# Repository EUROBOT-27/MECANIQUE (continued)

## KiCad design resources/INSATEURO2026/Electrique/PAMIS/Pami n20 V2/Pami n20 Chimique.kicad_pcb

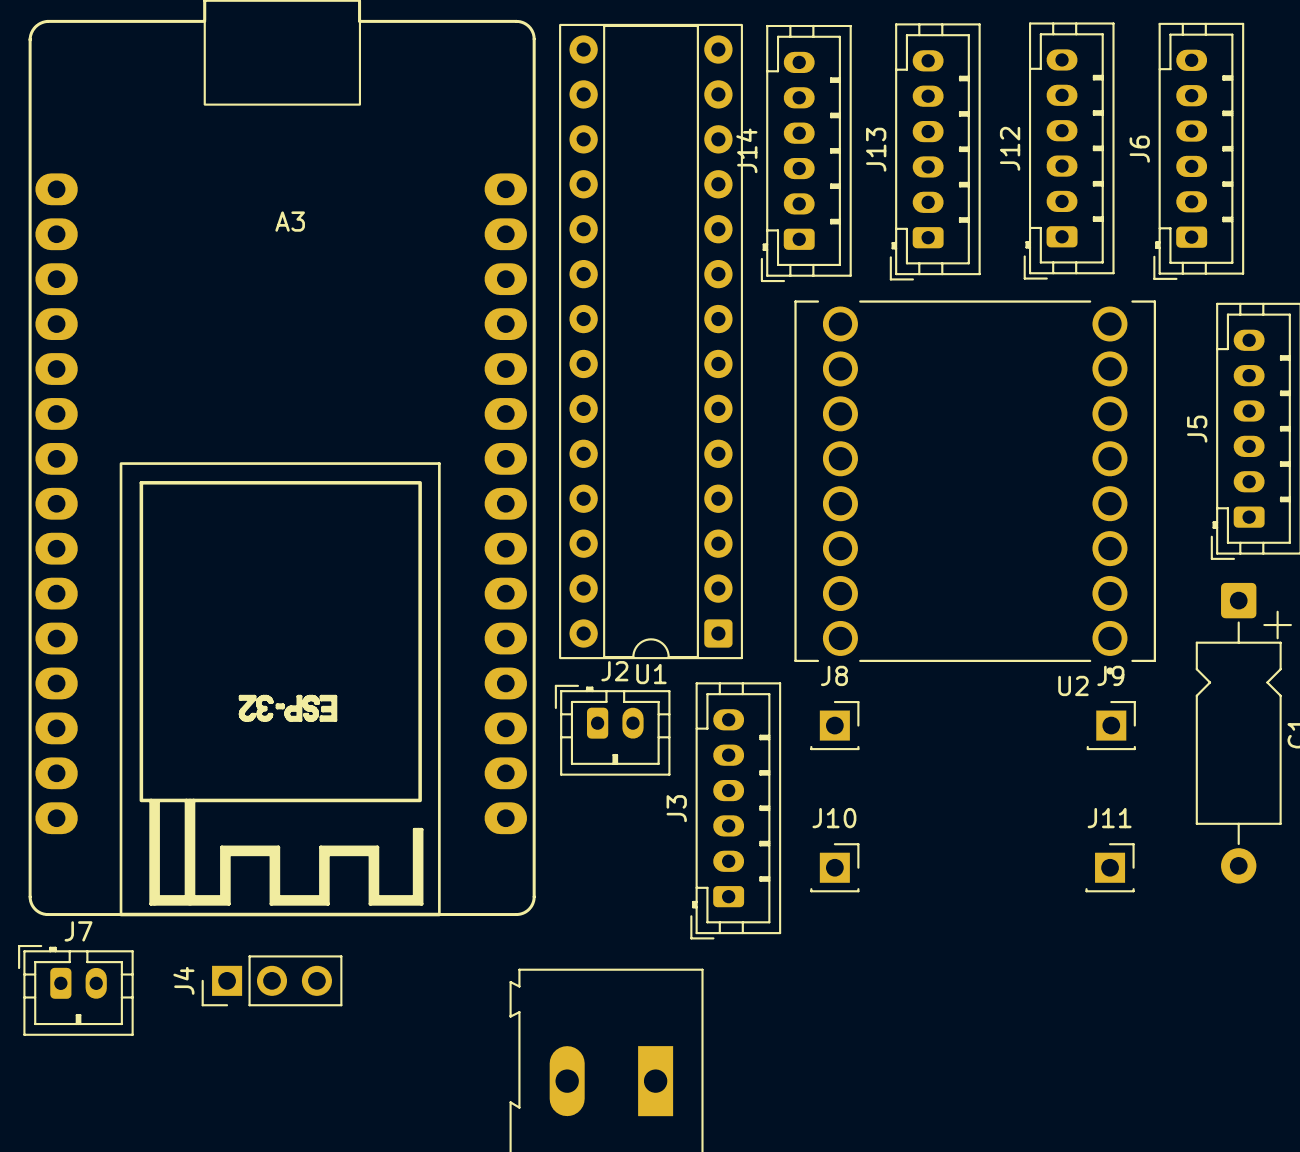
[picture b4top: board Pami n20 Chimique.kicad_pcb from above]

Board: 2 copper layers, 18 parts (0 on the bottom side), 31 nets, no tracks yet.

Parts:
A3: ESP32_DevKit_V1_DOIT_30GPIOs; DOIT_ESP32_DEVKIT_30Pins
C1: C_Polarized; CP_Axial_L10.0mm_D4.5mm_P15.00mm_Horizontal
J1: Screw_Terminal_01x02; TerminalBlock_Altech_AK300-2_P5.00mm
J2: URG; JST_PH_B2B-PH-K_1x02_P2.00mm_Vertical
J3: ENC2; JST_PH_B6B-PH-K_1x06_P2.00mm_Vertical
J4: Servo Connector; PinHeader_1x03_P2.54mm_Vertical
J5: ENC1; JST_PH_B6B-PH-K_1x06_P2.00mm_Vertical
J6: TOF1; JST_PH_B6B-PH-K_1x06_P2.00mm_Vertical
J7: Jack; JST_PH_B2B-PH-K_1x02_P2.00mm_Vertical
J8, J9, J10, J11: PINHD_1x1_Female; PinSocket_1x01_P2.54mm_Vertical
J12: TOF2; JST_PH_B6B-PH-K_1x06_P2.00mm_Vertical
J13: TOF3; JST_PH_B6B-PH-K_1x06_P2.00mm_Vertical
J14: TOF4; JST_PH_B6B-PH-K_1x06_P2.00mm_Vertical
U1: MCP23017_SP; DIP-28_W7.62mm_Socket
U2: ROB-14450; MODULE_ROB-14450

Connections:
+3.3V: A3.1 (3.3V), C1.1, J6.3, J12.3, J13.3, J14.3, U1.9 (VDD), U2.2 (VCC)
+5V: A3.30 (VIN), J3.2, J4.2, J5.2, J9.1, U2.1 (VM), U2.13 (STBY)
A1: J5.1, U2.4 (A01)
A2: J5.6, U2.5 (A02)
B1: J3.1, U2.7 (B01)
B2: J3.6, U2.6 (B02)
ENC1_A: A3.22 (ADC1_CH4/D33), J5.4
ENC1_B: A3.21 (ADC1_CH4/D32), J5.3
ENC2_A: A3.20 (ADC1_CH7/D35), J3.4
ENC2_B: A3.19 (ADC1_CH6/D34), J3.3
GND: A3.2 (GND), C1.2, J1.1, J3.5, J4.3, J5.5, J6.4, J7.2, J10.1, J11.1, J12.4, J13.4, J14.4, U1.10 (VSS), U1.15 (A0), U1.16 (A1), U1.17 (A2), U2.3 (GND), U2.8 (GND), U2.9 (GND)
GPIO1: J6.2, U1.1 (GPB0)
GPIO2: J12.2, U1.2 (GPB1)
GPIO3: J13.2, U1.3 (GPB2)
GPIO4: J14.2, U1.4 (GPB3)
JACK: A3.15 (D23), J7.1
M1_PWM: A3.8 (D5), U2.16 (PWMA)
M2_PWM: A3.27 (ADC2_CH5/D12), U2.10 (PWMB)
MOT_AIN1: U1.27 (GPA6), U2.14 (AI1)
MOT_AIN2: U1.28 (GPA7), U2.15 (AI2)
MOT_BIN1: U1.26 (GPA5), U2.12 (BI1)
MOT_BIN2: U1.25 (GPA4), U2.11 (BI2)
unnamed: J1.2, J2.1
SCL: A3.14 (D22/SCL), J6.5, J12.5, J13.5, J14.5, U1.12 (SCK)
SDA: A3.11 (D21/SDA), J6.6, J12.6, J13.6, J14.6, U1.13 (SDA)
SERVO_PWM: A3.9 (D18), J4.1
Supply: J2.2, J8.1
XShunt1: J6.1, U1.24 (GPA3)
XShunt2: J12.1, U1.23 (GPA2)
XShunt3: J13.1, U1.22 (GPA1)
XShunt4: J14.1, U1.21 (GPA0)

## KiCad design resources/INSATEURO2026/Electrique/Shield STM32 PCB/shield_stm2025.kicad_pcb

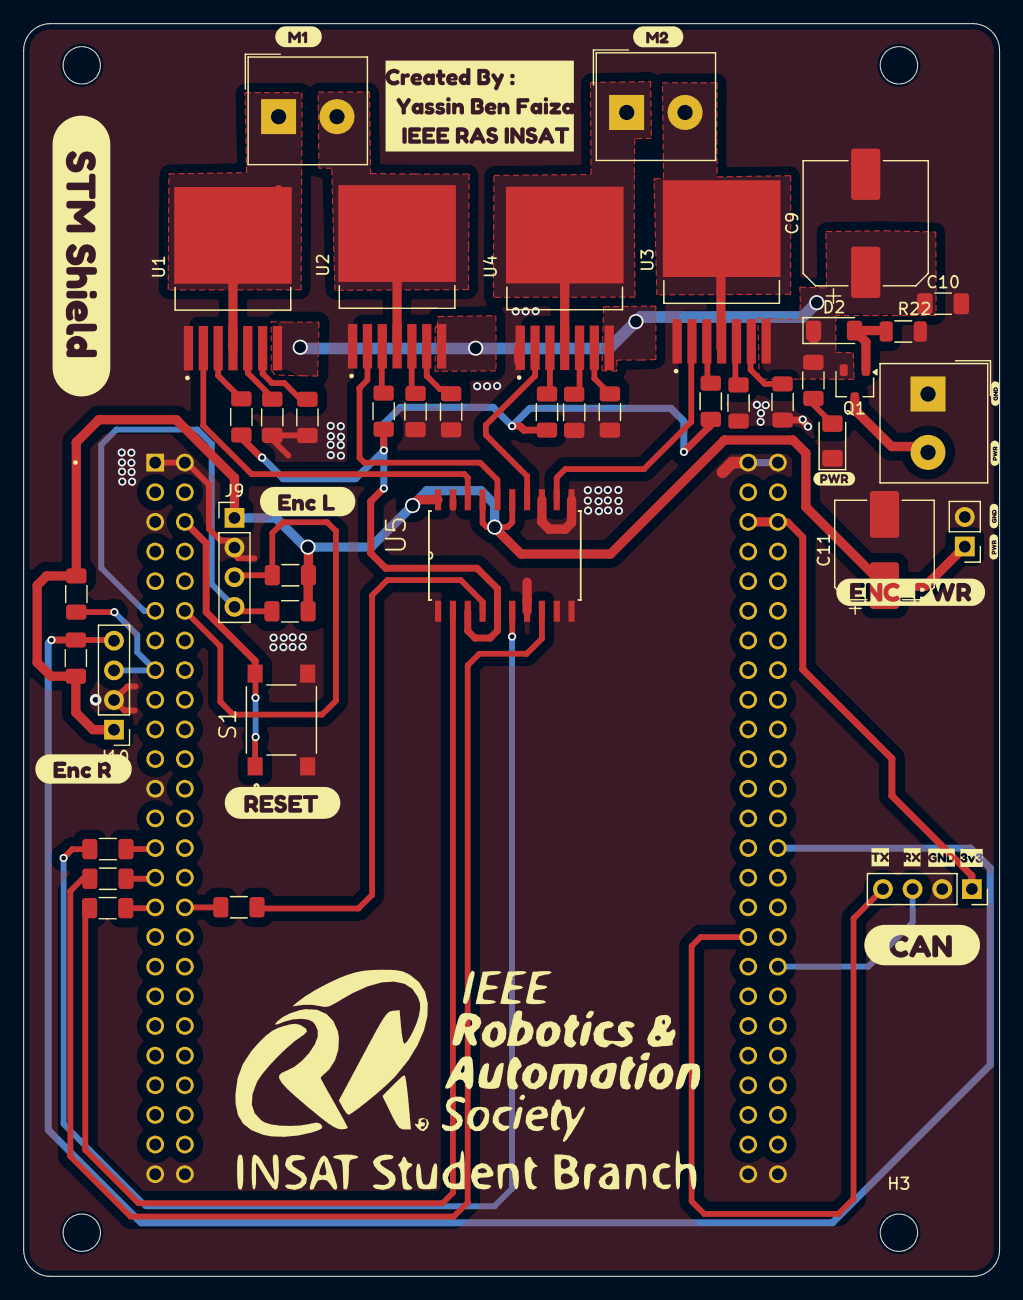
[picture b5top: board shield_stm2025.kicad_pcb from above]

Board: 2 copper layers, 83.6 x 107.3 mm, 64 parts (0 on the bottom side), 43 nets.

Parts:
C9: 470u; CP_Elec_10x10.5
C10: 100n; C_1206_3216Metric_Pad1.33x1.80mm_HandSolder
C11: 10u; CP_Elec_8x5.4
D1: LED; LED_1206_3216Metric_Pad1.42x1.75mm_HandSolder
D2: BZV55B10; D_MiniMELF
H1, H2, H3, H4: MountingHole; MountingHole_3.2mm_M3
J2: OUT M1; Altech_AK100_1x02_P5.00mm
J3: OUT M2; Altech_AK100_1x02_P5.00mm
J4: 24V input; Altech_AK100_1x02_P5.00mm
J6: CAN; PinSocket_1x04_P2.54mm_Vertical
J8: Alimentation; PinHeader_1x02_P2.54mm_Vertical
J9: Encoder_Left; PinHeader_1x04_P2.54mm_Vertical
J10: Encoder_Right; PinHeader_1x04_P2.54mm_Vertical
Q1: AO3401A; SOT-23W
R1, R2, R5, R6, R9, R10, R15, R16: 10K; R_1206_3216Metric_Pad1.30x1.75mm_HandSolder
R3, R4, R7, R8, R11, R12, R13, R14: 4.7K; R_1206_3216Metric_Pad1.30x1.75mm_HandSolder
R17, R18, R19, R20, R21: R; R_1206_3216Metric_Pad1.30x1.75mm_HandSolder
R22: 10K; R_1206_3216Metric
S1: PTS645SK50SMTR92LFS; SW_PTS645SK50SMTR92LFS
TB1: STM32F4DISCOVERY; MODULE_STM32F407G-DISC1
U1, U2, U3, U4: BTS7960B; DPAK127P1490X440-8N
U5: 74HC244; SOIC127P1032X265-20N
kibuzzard-6821E684: G***; kibuzzard-6821E684
kibuzzard-6821EA5D: G***; kibuzzard-6821EA5D
kibuzzard-6821EA78: G***; kibuzzard-6821EA78
kibuzzard-6821EB0D: G***; kibuzzard-6821EB0D
kibuzzard-6821EB1E: G***; kibuzzard-6821EB1E
kibuzzard-6821EB6B: G***; kibuzzard-6821EB6B
kibuzzard-6821FFFF: G***; kibuzzard-6821FFFF
kibuzzard-6824CA9A, kibuzzard-6824CA9A#2: G***; kibuzzard-6824CA9A
kibuzzard-6824CA75, kibuzzard-6824CA75#2: G***; kibuzzard-6824CA75
kibuzzard-6824CD1D: G***; kibuzzard-6824CD1D
kibuzzard-6824CD32: G***; kibuzzard-6824CD32
kibuzzard-6824CD49: G***; kibuzzard-6824CD49
kibuzzard-6824CD70: G***; kibuzzard-6824CD70
kibuzzard-6881FAE2: G***; kibuzzard-6881FAE2
kibuzzard-68220201: G***; kibuzzard-68220201
kibuzzard-68220375: G***; kibuzzard-68220375

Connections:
+3.3V: J6.1, TB1.P2_5 (3V), TB1.P2_6 (3V)
EN: R2.1, R6.1, R10.2, R15.2, U5.3 (2Y0), U5.5 (2Y1)
GND: C9.2, C10.2, C11.2, D1.1 (K), J4.1, J6.2, J8.2, J9.2, J10.2, R3.1, R4.2, R7.1, R8.2, R11.1, R12.2, R13.2, R14.1, R22.2, S1.3, S1.4, TB1.P1_1 (GND), TB1.P1_2 (GND), TB1.P1_5 (GND), TB1.P1_23 (GND), TB1.P1_49 (GND), TB1.P1_50 (GND), TB1.P2_1 (GND), TB1.P2_2 (GND), TB1.P2_49 (GND), TB1.P2_50 (GND), U1.1 (GND), U2.1 (GND), U3.1 (GND), U4.1 (GND), U5.1 (1OE), U5.7 (2Y2), U5.9 (2Y3), U5.10 (GND), U5.11 (2A3), U5.13 (2A2), U5.19 (2OE)
LPWM1: R1.1, TB1.P1_32 (PE14)
LPWM2: R16.1, TB1.P1_29 (PE11)
NRST: S1.1, S1.2, TB1.P1_6 (NRST)
unnamed: D1.2 (A), R17.2
unnamed: D2.2 (A), Q1.1 (G), R22.1
unnamed: J2.1, U1.4 (OUT), U1.8 (OUT)
unnamed: J2.2, U2.4 (OUT), U2.8 (OUT)
unnamed: J3.1, U4.4 (OUT), U4.8 (OUT)
unnamed: J3.2, U3.4 (OUT), U3.8 (OUT)
unnamed: J4.2, Q1.3 (D)
unnamed: R2.2, U1.3 (INH)
unnamed: R4.1, U1.6 (IS)
unnamed: R3.2, U1.5 (SR)
unnamed: R15.1, U2.3 (INH)
unnamed: R8.1, U2.6 (IS)
unnamed: R7.2, U2.5 (SR)
unnamed: R10.1, U3.3 (INH)
unnamed: R13.1, U3.6 (IS)
unnamed: R11.2, U3.5 (SR)
unnamed: R6.2, U4.3 (INH)
unnamed: R12.1, U4.6 (IS)
unnamed: R14.2, U4.5 (SR)
unnamed: R9.2, U5.2 (1A0)
unnamed: R1.2, U5.4 (1A1)
unnamed: R5.2, U5.6 (1A2)
unnamed: R16.2, U5.8 (1A3)
OUT1: U1.2 (IN), U5.18 (1Y0)
OUT2: U2.2 (IN), U5.16 (1Y1)
OUT3: U4.2 (IN), U5.14 (1Y2)
OUT4: U3.2 (IN), U5.12 (1Y3)
PA0: J9.3, R20.1, TB1.P1_12 (PA0-WKUP)
PA1: J9.4, R21.1, TB1.P1_11 (PA1)
PA5: J10.3, R18.1, TB1.P1_15 (PA5)
PB3: J10.4, R19.1, TB1.P2_28 (PB3)
RPWM1: R9.1, TB1.P1_31 (PE13)
RPWM2: R5.1, TB1.P1_27 (PE9)
RX: J6.3, TB1.P2_36 (PD0)
Supply: C9.1, C10.1, D2.1 (K), Q1.2 (S), R17.1, U1.7 (VS), U2.7 (VS), U3.7 (VS), U4.7 (VS)
TX: J6.4, TB1.P2_33 (PD1)
VCC: C11.1, J8.1, J9.1, J10.1, R18.2, R19.2, R20.2, R21.2, U5.15 (2A1), U5.17 (2A0), U5.20 (VCC)

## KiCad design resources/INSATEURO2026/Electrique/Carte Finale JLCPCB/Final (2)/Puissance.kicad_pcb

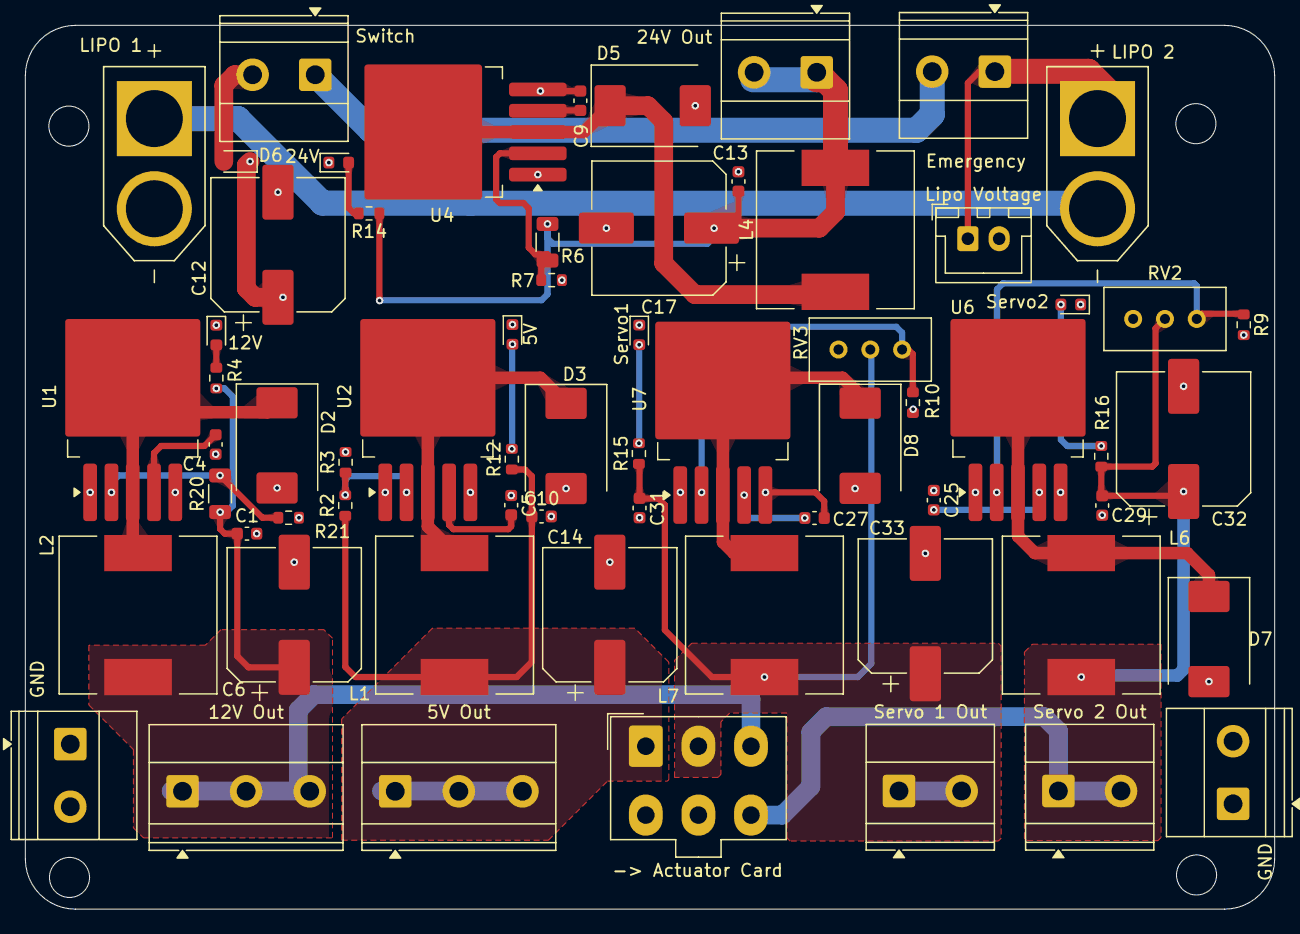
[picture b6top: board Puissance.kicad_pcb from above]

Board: 4 copper layers, 99.8 x 70.6 mm, 65 parts (0 on the bottom side), 31 nets.

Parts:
5V, 12V, 24V: LED; LED_0603_1608Metric
5V Out: 5V; TerminalBlock_Phoenix_MKDS-1,5-3-5.08_1x03_P5.08mm_Horizont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
12V Out: 12V; TerminalBlock_Phoenix_MKDS-1,5-3-5.08_1x03_P5.08mm_Horizont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
24V Out: 24V Out; TerminalBlock_Phoenix_MKDS-1,5-2_1x02_P5.00mm_Horizontal
-> Actuator Card: Conn_02x03; Molex_Mini-Fit_Jr_5566-06A_2x03_P4.20mm_Vertical
C1, C4, C5, C9, C10, C13, C25, C27, C29, C31: 105; C_0603_1608Metric
C6, C14, C17, C32, C33: 330u; CP_Elec_10x10.5
C12: 1000u; CP_Elec_10x10.5
D2, D3, D5, D7, D8: B540C; D_SMC
D6: SS34; D_SOD-323
Emergency: Emergency Stop; TerminalBlock_Phoenix_MKDS-1,5-2_1x02_P5.00mm_Horizontal
GND: ADJ out; TerminalBlock_Phoenix_MKDS-1,5-2_1x02_P5.00mm_Horizontal
GND : ADJ out; TerminalBlock_Phoenix_MKDS-1,5-2_1x02_P5.00mm_Horizontal
L1, L2, L4, L6, L7: 47uH; L_12x12mm_H6mm
LIPO 1, LIPO 2: XT60-M; AMASS_XT60-M
Lipo Voltage: LIPO 1 VOLT; JST_XH_B2B-XH-A_1x02_P2.50mm_Vertical
R2: 10K; R_0603_1608Metric
R3, R7, R9, R10: 3.3K; R_0603_1608Metric
R4: 1k; R_0603_1608Metric
R6: 60.4K; R_1206_3216Metric
R12: 220; R_0603_1608Metric
R14: 3.3k; R_0603_1608Metric
R15, R16: 1K; R_0603_1608Metric
R20: 13K; R_1206_3216Metric
R21: 1.5K; R_0603_1608Metric
RV2, RV3: R_Potentiometer; Potentiometer_Bourns_3296W_Vertical
Servo1, Servo2: LED; LED_0603_1608Metric
Servo 1 Out, Servo 2 Out: ADJ out; TerminalBlock_Phoenix_MKDS-1,5-2_1x02_P5.00mm_Horizontal
Switch: Master Switch; TerminalBlock_Phoenix_MKDS-1,5-2_1x02_P5.00mm_Horizontal
U1, U2, U4, U6, U7: XL4015; TO-263-5_TabPin3

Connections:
5V: 5V Out.1, 5V Out.2, 5V Out.3, -> Actuator Card.1, C10.1, C14.1, L1.2, R2.1, R12.1
12V: 12V Out.1, 12V Out.2, 12V Out.3, -> Actuator Card.3, C1.1, C6.1, L2.2, R4.1, R20.1
24V: 24V Out.1, 24V Out.2, C13.1, C17.1, L4.2, R6.1, R14.1
ADJ1: -> Actuator Card.6, C29.1, C32.1, L6.2, R16.1, RV2.2, Servo 2 Out.1, Servo 2 Out.2
GND: 5V.1 (K), 12V.1 (K), 24V.1 (K), -> Actuator Card.4, -> Actuator Card.5, C1.2, C6.2, C10.2, C12.2, C13.2, C14.2, C17.2, C29.2, C31.2, C32.2, C33.2, D2.2 (A), D3.2 (A), D5.2 (A), D7.2 (A), D8.2 (A), GND.1, GND.2, GND.1, GND.2, LIPO 1.N (NEG), Lipo Voltage.2, R3.2, R7.2, R9.2, R10.2, R21.2, RV2.3, RV3.3, Servo1.1 (K), Servo2.1 (K), U1.1 (GND), U2.1 (GND), U4.1 (GND), U6.1 (GND), U7.1 (GND)
unnamed: D2.1 (K), L2.1, U1.3 (SW)
unnamed: D3.1 (K), L1.1, U2.3 (SW)
unnamed: 12V.2 (A), R4.2
unnamed: D5.1 (K), L4.1, U4.3 (SW)
unnamed: D7.1 (K), L6.1, U6.3 (SW)
unnamed: D8.1 (K), L7.1, U7.3 (SW)
unnamed: 5V.2 (A), R12.2
unnamed: 24V.2 (A), R14.2
unnamed: R15.2, Servo1.2 (A)
unnamed: R16.2, Servo2.2 (A)
unnamed: LIPO 1.P (POS), LIPO 2.N (NEG)
unnamed: Emergency.1, LIPO 2.P (POS), Lipo Voltage.1
unnamed: Emergency.2, Switch.1
unnamed: R20.2, R21.1, U1.2 (FB)
unnamed: C4.2, U1.4 (VC)
unnamed: R2.2, R3.1, U2.2 (FB)
unnamed: C5.2, U2.4 (VC)
unnamed: R6.2, R7.1, U4.2 (FB)
unnamed: C9.2, U4.4 (VC)
unnamed: R9.1, RV2.1, U6.2 (FB)
unnamed: C25.2, U6.4 (VC)
unnamed: R10.1, RV3.1, U7.2 (FB)
unnamed: C27.2, U7.4 (VC)
SERVO: -> Actuator Card.2, C31.1, C33.1, L7.2, R15.1, RV3.2, Servo 1 Out.1, Servo 1 Out.2
SUPPLY: D6.2 (A), Switch.2
VDC: C4.1, C5.1, C9.1, C12.1, C25.1, C27.1, D6.1 (K), U1.5 (VIN), U2.5 (VIN), U4.5 (VIN), U6.5 (VIN), U7.5 (VIN)

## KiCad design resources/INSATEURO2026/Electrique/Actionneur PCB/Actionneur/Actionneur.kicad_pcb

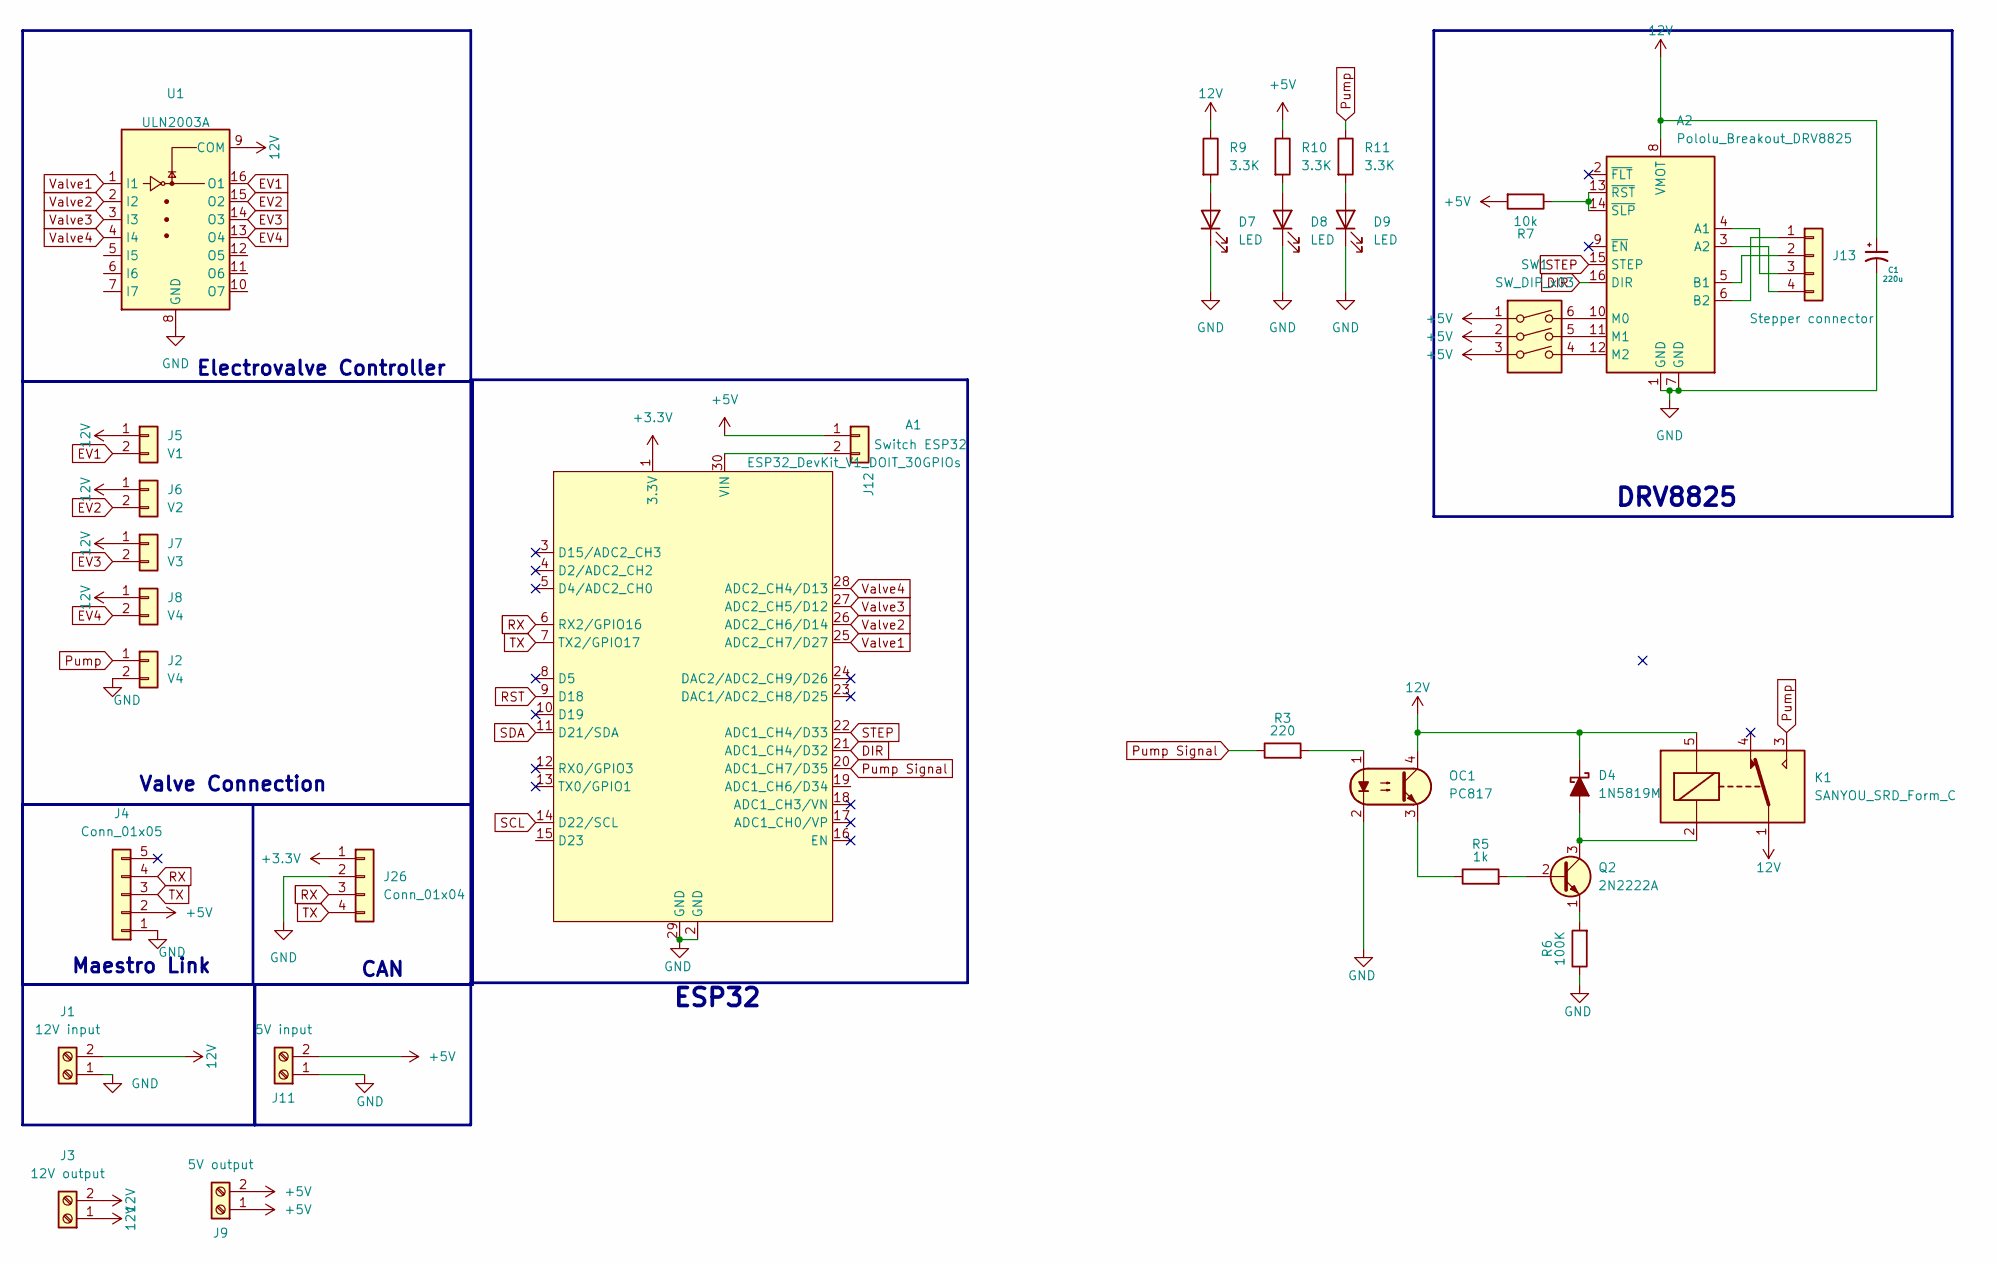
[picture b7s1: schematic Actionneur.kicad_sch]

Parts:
A1: ESP32_DevKit_V1_DOIT_30GPIOs; DOIT_ESP32_DEVKIT_30Pins
A2: Pololu_Breakout_DRV8825; Pololu_Breakout-16_15.2x20.3mm
C1: 220u; CP_Elec_10x10.5
D4: 1N5819M; D_SMC
D7, D8, D9: LED; LED_0603_1608Metric
J1: 12V input; Altech_AK100_1x02_P5.00mm
J2, J8: V4; JST_PH_B2B-PH-K_1x02_P2.00mm_Vertical
J3: 12V output; Altech_AK100_1x02_P5.00mm
J4: Conn_01x05; JST_EH_B5B-EH-A_1x05_P2.50mm_Vertical
J5: V1; JST_PH_B2B-PH-K_1x02_P2.00mm_Vertical
J6: V2; JST_PH_B2B-PH-K_1x02_P2.00mm_Vertical
J7: V3; JST_PH_B2B-PH-K_1x02_P2.00mm_Vertical
J9: 5V output; Altech_AK100_1x02_P5.00mm
J11: 5V input; Altech_AK100_1x02_P5.00mm
J12: Switch ESP32; PinHeader_1x02_P1.00mm_Vertical
J13: Stepper connector; JST_EH_B4B-EH-A_1x04_P2.50mm_Vertical
J26: Conn_01x04; JST_EH_B4B-EH-A_1x04_P2.50mm_Vertical
K1: SANYOU_SRD_Form_C; Relay_SPDT_SANYOU_SRD_Series_Form_C
OC1: PC817; Vishay_CNY64
Q2: 2N2222A; TO-18-3_EBC
R3: 220; R_0603_1608Metric
R5: 1k; R_0603_1608Metric
R6: 100K; R_0603_1608Metric
R7: 10k; R_Axial_DIN0204_L3.6mm_D1.6mm_P7.62mm_Horizontal
R9, R10, R11: 3.3K; R_0603_1608Metric
SW1: SW_DIP_x03; SW_DIP_SPSTx03_Slide_9.78x9.8mm_W7.62mm_P2.54mm
U1: ULN2003A; DIP-16_W7.62mm

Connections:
12V: A2.8 (VMOT), C1.1, D4.1 (K), J1.2, J3.1, J3.2, J5.1, J6.1, J7.1, J8.1, K1.1, K1.5, OC1.4, R9.1, U1.9 (COM)
+3.3V: A1.1 (3.3V), J26.1
+5V: J4.2, J9.1, J9.2, J11.2, J12.1, R7.2, R10.1, SW1.1, SW1.2, SW1.3
DIR: A1.21 (ADC1_CH4/D32), A2.16 (DIR)
EV1: J5.2, U1.16 (O1)
EV2: J6.2, U1.15 (O2)
EV3: J7.2, U1.14 (O3)
EV4: J8.2, U1.13 (O4)
GND: A1.2 (GND), A1.29 (GND), A2.1 (GND), A2.7 (GND), C1.2, D7.1 (K), D8.1 (K), D9.1 (K), J1.1, J2.2, J4.1, J11.1, J26.2, OC1.2, R6.1, U1.8 (GND)
unnamed: A1.30 (VIN), J12.2
unnamed: A2.4 (A1), J13.3
unnamed: A2.3 (A2), J13.4
unnamed: A2.5 (B1), J13.2
unnamed: A2.6 (B2), J13.1
unnamed: A2.10 (M0), SW1.6
unnamed: A2.11 (M1), SW1.5
unnamed: A2.12 (M2), SW1.4
unnamed: A2.13 (~RST), A2.14 (~SLP), R7.1
unnamed: D4.2 (A), K1.2, Q2.3 (C)
unnamed: D7.2 (A), R9.2
unnamed: D8.2 (A), R10.2
unnamed: D9.2 (A), R11.2
unnamed: OC1.1, R3.2
unnamed: OC1.3, R5.1
unnamed: Q2.2 (B), R5.2
unnamed: Q2.1 (E), R6.2
Pump: J2.1, K1.3, R11.1
Pump Signal: A1.20 (ADC1_CH7/D35), R3.1
RST: A1.9 (D18)
RX: A1.6 (RX2/GPIO16), J4.4, J26.3
SCL: A1.14 (D22/SCL)
SDA: A1.11 (D21/SDA)
STEP: A1.22 (ADC1_CH4/D33), A2.15 (STEP)
TX: A1.7 (TX2/GPIO17), J4.3, J26.4
Valve1: A1.25 (ADC2_CH7/D27), U1.1 (I1)
Valve2: A1.26 (ADC2_CH6/D14), U1.2 (I2)
Valve3: A1.27 (ADC2_CH5/D12), U1.3 (I3)
Valve4: A1.28 (ADC2_CH4/D13), U1.4 (I4)

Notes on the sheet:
DRV8825
ESP32
Electrovalve Controller
CAN
Valve Connection
Maestro Link

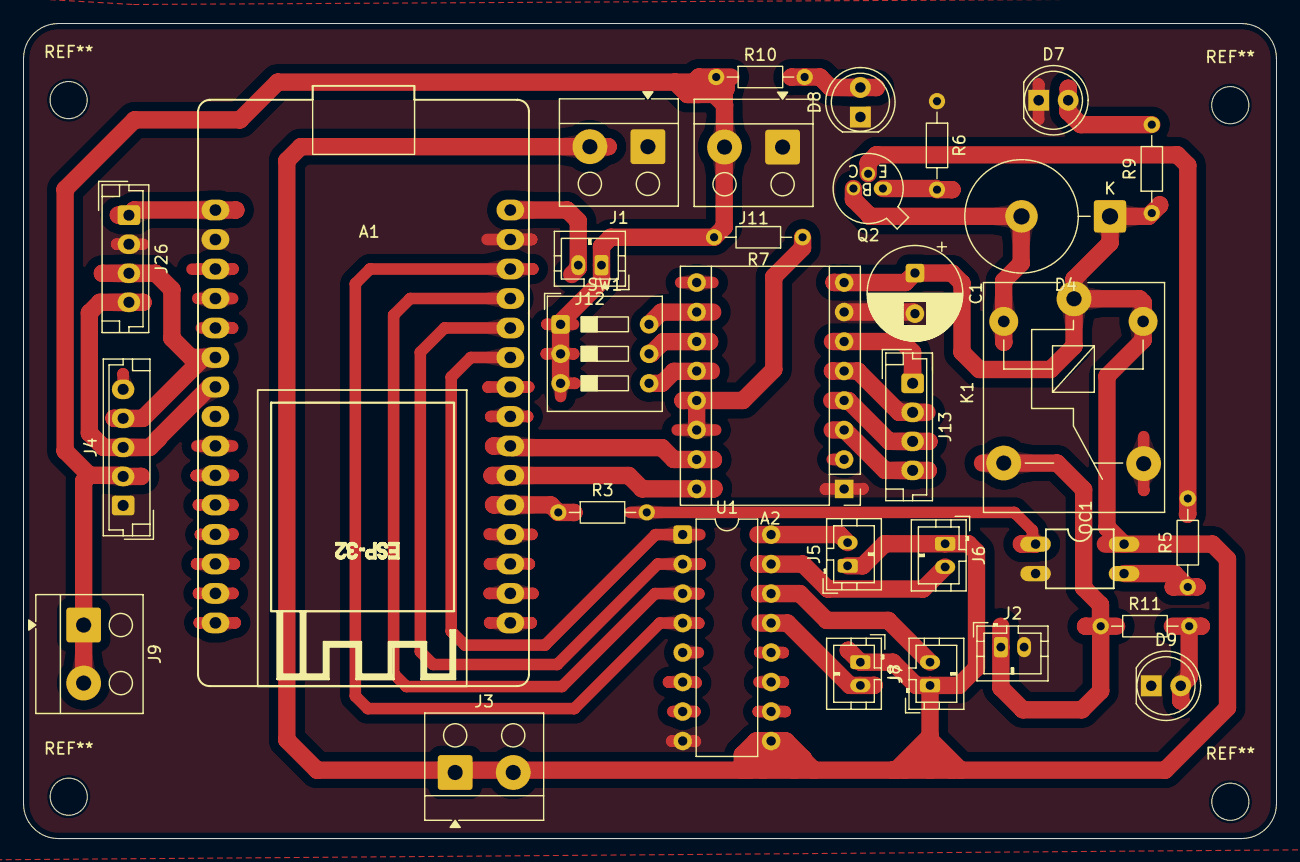
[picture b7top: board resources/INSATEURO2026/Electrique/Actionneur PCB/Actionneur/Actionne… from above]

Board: 2 copper layers, 107.9 x 70.2 mm, 32 parts (0 on the bottom side), 35 nets.

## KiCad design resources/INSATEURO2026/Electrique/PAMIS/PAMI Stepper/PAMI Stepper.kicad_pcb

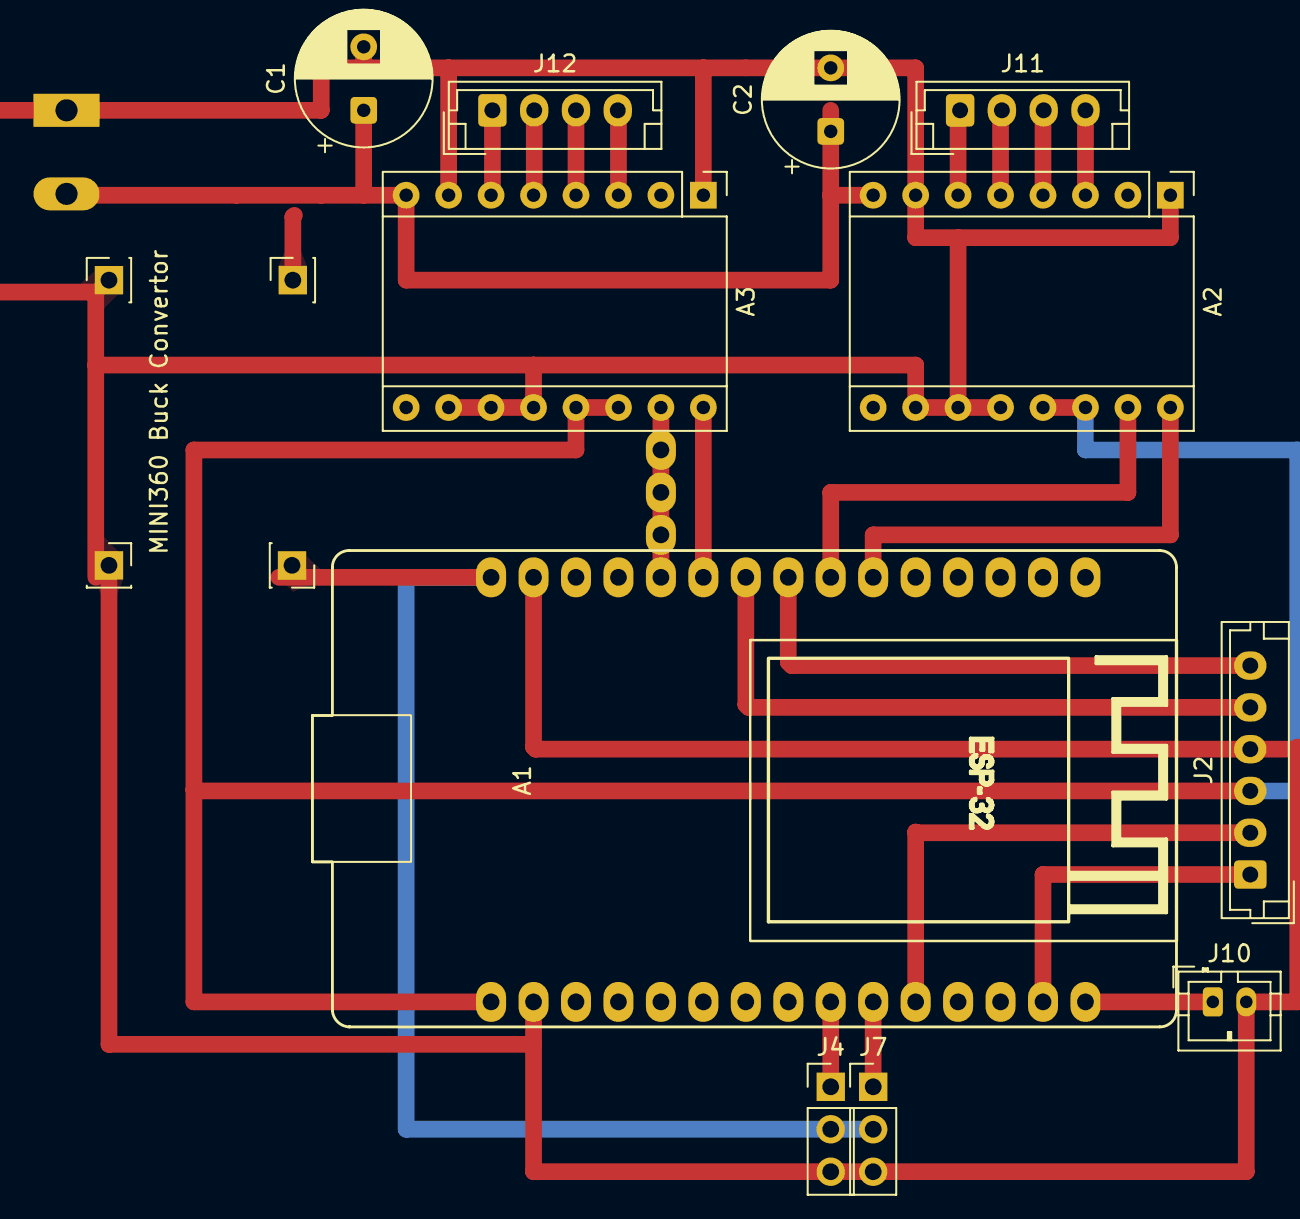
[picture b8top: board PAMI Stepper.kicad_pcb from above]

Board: 2 copper layers, 16 parts (1 on the bottom side), 23 nets.

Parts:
A1: ESP32_DevKit_V1_DOIT_30GPIOs; DOIT_ESP32_DEVKIT_30Pins
A2, A3: Pololu_Breakout_DRV8825; Pololu_Breakout-16_15.2x20.3mm
C1, C2: 220u; CP_Radial_D8.0mm_P3.80mm
J1: Screw_Terminal_01x02; TerminalBlock_Altech_AK300-2_P5.00mm
J2: Mot 1; JST_EH_B6B-EH-A_1x06_P2.50mm_Vertical
J4, J7: Servo Connector; PinHeader_1x03_P2.54mm_Vertical
J8, J9, J11#2: PINHD_1x1_Female; PinSocket_1x01_P2.54mm_Vertical
J10: Jack; JST_PH_B2B-PH-K_1x02_P2.00mm_Vertical
J10#2: MINI360 Buck Convertor; PinSocket_1x01_P2.54mm_Vertical
J11, J12: Stepper connector; JST_EH_B4B-EH-A_1x04_P2.50mm_Vertical

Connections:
12V: A2.8 (VMOT), A3.8 (VMOT), C1.1, C2.1, J1.2
+3.3V: A1.1 (3.3V), A2.13 (~RST), A2.14 (~SLP), A3.13 (~RST), A3.14 (~SLP), J2.3
+5V: A1.30 (VIN), J4.2, J7.2, J9.1
DIR: A1.21 (ADC1_CH4/D32), A2.16 (DIR)
DIR2: A1.25 (ADC2_CH7/D27), A3.16 (DIR)
GND: A1.2 (GND), A1.29 (GND), A2.1 (GND), A2.7 (GND), A2.10 (M0), A2.11 (M1), A2.12 (M2), A3.1 (GND), A3.7 (GND), A3.10 (M0), A3.11 (M1), A3.12 (M2), C1.2, C2.2, J1.1, J2.4, J4.3, J7.3, J10.2, J10#2.1, J11#2.1
GPIO: A1.24 (DAC2/ADC2_CH9/D26), J2.5
JACK: A1.15 (D23), J10.1
unnamed: A2.4 (A1), J11.3
unnamed: A2.3 (A2), J11.4
unnamed: A2.5 (B1), J11.2
unnamed: A2.6 (B2), J11.1
unnamed: A3.4 (A1), J12.3
unnamed: A3.3 (A2), J12.4
unnamed: A3.5 (B1), J12.2
unnamed: A3.6 (B2), J12.1
SCL: A1.14 (D22/SCL), J2.1
SDA: A1.11 (D21/SDA), J2.2
SERVO_PWM1: A1.9 (D18), J4.1
SERVO_PWM2: A1.10 (D19), J7.1
STEP: A1.22 (ADC1_CH4/D33), A2.15 (STEP)
STEP2: A1.26 (ADC2_CH6/D14), A3.15 (STEP)
XShunt1: A1.23 (DAC1/ADC2_CH8/D25), J2.6

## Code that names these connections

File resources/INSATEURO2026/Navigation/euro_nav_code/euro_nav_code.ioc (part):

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Mcu.Name=STM32F407V(E-G)Tx
Mcu.Package=LQFP100
Mcu.UserName=STM32F407VGTx
PA0-WKUP.Signal=S_TIM5_CH1
PA1.Signal=S_TIM5_CH2
PA5.Signal=S_TIM2_CH1_ETR
PB3.Signal=S_TIM2_CH2
PD0.Mode=CAN_Activate
PD0.Signal=CAN1_RX
PD1.Mode=CAN_Activate
PD1.Signal=CAN1_TX
PE11.Signal=S_TIM1_CH2
PE13.Signal=S_TIM1_CH3
PE14.Signal=S_TIM1_CH4
PE9.Signal=S_TIM1_CH1
PH0-OSC_IN.Mode=HSE-External-Oscillator
PH0-OSC_IN.Signal=RCC_OSC_IN
PH1-OSC_OUT.Mode=HSE-External-Oscillator
PH1-OSC_OUT.Signal=RCC_OSC_OUT
RCC.HSE_VALUE=8000000
RCC.SYSCLKFreq_VALUE=168000000
RCC.SYSCLKSource=RCC_SYSCLKSOURCE_PLLCLK
board=STM32F407G-DISC1
boardIOC=true
